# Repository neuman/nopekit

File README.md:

# nopekit

<p align="center">
<picture>
  <source media="(prefers-color-scheme: dark)" srcset="docs/img/nopey.png">
  
</picture>
</p>

## What Is Nopekit?

**Nopekit gives your AI agent engineering checks that can say “nope.”** It's a plugin for Claude Code, Codex and Cursor that helps you turn an idea into a physical design, test it against math, physics and engineering tools, and see what still needs work.

It's based on the [Grounding by Falsification](https://github.com/neuman/nopekit/blob/main/grounding_by_falsification.pdf) approach. AI has gotten very good at making believable proposals for all sorts of things both digital and physical but it is especially good at coding. The problem is that it's still not great at figuring out which proposals are actually good on its own. Grounding by falsification is the idea that we need to wrap AI with something outside itself that can check its work and say "nope" using trusted reasoning/math/physics/etc. Nopekit turns that approach into an extensible framework with room for plugins that can falsify proposals across any domain but especially physical design work.

**You describe what you want. The agent proposes a design. Independent checks try to break it.** Nopekit records the results and the reasons behind each design choice, then shows them on a project site. When the design changes, affected results become stale until checked again. Assumptions and tests that need a real prototype stay visible.

For example: “This shelf must carry 10 kg” becomes a load and a deflection limit. The agent designs a bracket; a beam check rejects it if it sags too far; a printability check rejects walls that are too thin. You can follow what failed, what changed, and why the next candidate is better.

[See It In Action](#see-it-in-action) · [Built In Packs](#built-in-packs) · [External Packs](#external-packs) · [Getting Started](#getting-started)

## See It In Action

**[PETGasus](https://neuman.github.io/PETGasusDrone/) is a quadcopter with a frame designed to print in one piece.** Its project site connects the design you can see with the requirements, decisions and evidence behind it.

[**Explore the live site →**](https://neuman.github.io/PETGasusDrone/) · [**Read the project repository →**](https://github.com/neuman/petgasusdrone)

The design history includes disconnected frames, thin walls and a frame that sagged far more than its optimizer predicted. Those rejected candidates are part of the record. The site shows what passed, what failed and what still waits on a physical build.

For smaller starting points, explore the [bracket example](examples/bracket/README.md), which runs without extra dependencies, or the [motorcycle airflow example](examples/motorbike/README.md), which uses OpenFOAM and ParaView.

## Built In Packs

Packs give the agent tools for a domain. A **proposer** makes a candidate; a **falsifier**, called a **gate**, checks it. One design can use several packs: a drone frame needs structural, printing, geometry and cost checks.

**Falsifiers**

These thirteen packs ship with Nopekit. The images show designs, results or illustrations of what each pack can check; click a pack name for its gates, sources, setup and limits.

| Example | Pack and what it checks | Basis and sources |
|---|---|---|
| <br>Check the exported shape with a different solver | [**topology-simp**](packs/topology-simp/PACK.md) · 4 gates<br>Material volume, static displacement and stress in a stated region. CalculiX meshes the exported STL independently of the optimizer; checks include mesh refinement and load equilibrium. | **3 established · 1 model-only**<br>trimesh and CalculiX results, with model-input guards. Requires trimesh, NumPy, Gmsh and CalculiX 2.21. Linear isotropic static checks; printing and physical tests remain separate. |
| <br>Air around a motorcycle and rider | [**aero-openfoam**](packs/aero-openfoam/PACK.md) · 9 gates<br>Drag, mesh quality, convergence and wall treatment for turbulent external flow. The motorcycle example's drag claim is still unresolved. | **3 established · 4 sourced · 2 model-only**<br>OpenFOAM; published domain, convergence and grid-error methods. Needs ESI OpenFOAM v2606; ParaView 6.2 for pictures. |
| <br>Do all these parts fit together? | [**cad-solid**](packs/cad-solid/PACK.md) · 8 gates<br>Closed solids, collisions, clearances, wall thickness and whether every part is held in the assembly. | **2 established · 6 model-only**<br>trimesh's volume verdict and manifold3d's clearance; Nopekit's geometry checks. Needs trimesh and NumPy; the clearance gate needs manifold3d and the wall gate SciPy or NetworkX. |
| <br>A drone frame designed to print in one piece | [**fdm-print**](packs/fdm-print/PACK.md) · 8 gates<br>Thin walls, overhangs, bridges, bed fit, layer direction, estimated print time and a slice on OrcaSlicer. | **8 model-only**<br>Printing heuristics with documented thresholds. Mesh checks need trimesh and NumPy; the slicer gate needs OrcaSlicer 2.4.2. A pass still needs a real print. |
| <br>The pack's own test board, as KiCad draws it | [**pcb-kicad**](packs/pcb-kicad/PACK.md) · 18 gates<br>Design rules with every custom rule probed, open connections, schematic agreement, pin names, trace heating, a fab's limits, circuit simulation, enclosure fit, land patterns against the vendor's drawing, a cell's charge window, charge limits, fault current and cutoff, connectors that can mate the wrong way, USB-C termination and radio antenna keep-outs. | **6 established · 9 sourced · 3 model-only**<br>KiCad, ngspice and CadQuery; IPC-2221, IEC 60949, the USB Type-C specification, module vendors' antenna guidance and fabricator limits. A clean rule check does not establish a correct circuit. |
| Firmware that CI really builds, that fits its flash, wakes from deep sleep and stays inside its radio grant | [**firmware-ci**](packs/firmware-ci/PACK.md) · 5 gates<br>A CI job that can read green on a failed build, then a replay of that job with act in its own containers: the build, the image against its flash region, the deep-sleep wake source and the Bluetooth LE transmit setting. The build and image checks serve any stack that builds in a GitHub Actions job on Linux; the wake rule covers ESP-IDF and ZMK, the transmit rule Zephyr, nRF Connect SDK and ESP-IDF on ESP32-C3 and S3, and each skips other stacks by name. | **1 established · 4 sourced**<br>The toolchain's own exit code in the job's container; GitHub's documented shell behaviour, the bootloader's or partition table's layout, and each stack's sleep and Kconfig sources. Needs act 0.2.97, Docker and Git, plus PyYAML; the baseline's ESP-IDF image is about 5.4 GB. The transmit limit is your claim: the pack cannot say which radio grant applies. |
| Can the smallest hands in the range reach every control? | [**hand-ergonomics**](packs/hand-ergonomics/PACK.md) · 2 gates<br>The share of a measured population whose thumb or index finger reaches every control from its grip, counted subject by subject, on a declared layout that must match the exported scene. | **1 sourced · 1 model-only**<br>ANSUR 1988's per-subject hand data (public domain), shipped with its hashes. The reach count needs no extra dependencies; the layout check needs trimesh, NumPy and manifold3d. Comfort, width and mass stay with a person who holds a print. |
| <br>Beam-pack baseline, illustrated | [**beam-analytic**](packs/beam-analytic/PACK.md) · 8 gates<br>Bending, sag, buckling, shear and fastener bearing, with guards on where beam theory applies. | **7 sourced · 1 model-only**<br>Standard strength-of-materials formulae. No extra dependencies. Applies to beam-like members, not arbitrary meshes. |
| <br>Pressure loss through an oil channel | [**cfd-openfoam**](packs/cfd-openfoam/PACK.md) · 6 gates<br>Laminar pressure drop after checking flow regime, mesh quality, convergence and mesh independence. | **3 established · 2 sourced · 1 model-only**<br>OpenFOAM and published grid-convergence methods. Needs ESI OpenFOAM v2606; ParaView 6.2 for pictures. |
| <br>Solar charging over two weeks | [**thermal-analytic**](packs/thermal-analytic/PACK.md) · 11 gates<br>Heat loss, cooling, temperature, fins, solar collection, stagnation and a sealed handheld's average skin temperature. | **10 sourced · 1 model-only**<br>Heat-transfer correlations; Duffie & Beckman and ASHRAE solar models. No extra dependencies. |
| <br>A solar Stirling system over a day | [**openmodelica**](packs/openmodelica/PACK.md) · 8 gates<br>Equation balance, compilation, simulation completion and simulated values against their limits. | **4 established · 4 model-only**<br>OpenModelica's own checks and results, plus source and consistency checks. Solver gates need `omc`. |
| <br>A hull that must float and stay upright | [**fluids-analytic**](packs/fluids-analytic/PACK.md) · 7 gates<br>Buoyancy, freeboard, stability, drag and pipe pressure loss. | **7 sourced**<br>Textbook hydrostatics and flow correlations, within their stated regimes. No extra dependencies. |
| <br>The whole build against its budget | [**sourcing**](packs/sourcing/PACK.md) · 7 gates<br>Missing prices, cost overruns, lead times, minimum orders and single-source parts. | **1 sourced · 6 model-only**<br>Vendor process rules and procurement checks on your recorded bill of materials. Offline; no live stock search. No extra dependencies. |

**How much should you trust a check?** Each gate declares where its logic comes from:

- **Established:** an existing tool's own verdict, such as KiCad's design-rule check. Trust extends as far as that tool and the problem you gave it.
- **Sourced:** a formula or rule from a cited textbook, standard or datasheet. Trust depends on the source and its range of applicability.
- **Model-only:** logic without an independent source. Its controls show it can fail; they do not establish that its reasoning is correct.

Before a gate's passes count, it must pass a known-good input and reject a known-bad one. That qualification is separate from its basis. **Skipped, crashed and stale checks never count as passes.** The report shows both the outcome and the basis so you can judge the evidence.

**Proposers**

The agent itself is the everyday proposer, writing and changing your design. Built-in packs also ship dedicated proposal tools:

| Example | Proposer | Tool and trust |
|---|---|---|
| <br>Find where the material earns its weight | [**topology-simp: 3D topology optimization**](packs/topology-simp/PACK.md)<br>Give it loads, supports, keep-outs and a material budget. SIMP proposes a 3D density field for your model to turn into a part. | **Sourced:** SIMP, density filtering and projection from published methods. Extracted from PETGasus. NumPy, SciPy and Numba; pyamg for larger solves. Its own score is a proposal, never structural proof. |
| <br>The pack's test board, routed again | [**pcb-kicad: autoroute**](packs/pcb-kicad/PACK.md)<br>Turn an unrouted KiCad board into a routed candidate. | **Freerouting**, an established autorouter. Its output is a proposal; KiCad gates check the adopted board. Requires pcbnew, Java and Freerouting. |
| Schematic for a generated board | [**pcb-kicad: schematic_from_board**](packs/pcb-kicad/PACK.md)<br>Write a KiCad schematic from a board's pad nets, so ERC, parity and pin names can run on a board with no drawn schematic. | **Model-only:** this pack's own writer, on KiCad's stock symbols mapped by a person part by part. Its output is a proposal; KiCad's parity check compares the adopted schematic with the board. Needs only KiCad's symbol library. |
| Power records for a board that carries a cell | [**pcb-kicad: battery_record_draft**](packs/pcb-kicad/PACK.md)<br>Draft the cell, charger, protector, conductor, mating, USB-C and rail records that the power rules read, from a board's parts, pin names and copper. | **Model-only:** this pack's own reader of the board. Every datasheet number, choice and source is left as a FILL value, and every power rule refuses the draft until a person fills them. Standard library only. |
| Where each thumb reaches on the face | [**hand-ergonomics: reach_envelope**](packs/hand-ergonomics/PACK.md)<br>Map where each grip's thumb and index finger reach, as a share of the population; count how many controls of a pitch fit in reach; give the grip spacing and design ranges for hand size. | **Sourced:** ANSUR 1988's per-subject hand data, the table `ergo.digit_reach` counts. A share on the map is for one point; the gate counts every control at once. Its maps are proposals; the reach gate judges the layout you adopt. matplotlib draws the map where it is installed. |

## External Packs

**A pack can live in its own Git repository.** You can share domain knowledge, wrap another engineering tool, or keep a project's custom checks alongside its design without changing Nopekit itself.

A standalone pack has a `pack.json` manifest, a `PACK.md` explaining its scope, and the gates, proposers, references and test fixtures it needs. Clone it into your project's `.nopekit/packs/<pack-name>/`, or into `~/.nopekit/packs/<pack-name>/` to make it discoverable across projects. `NOPEKIT_PACK_PATH` can point to other directories containing packs.

Then enable it by the name in its manifest:

```sh
nopekit packs list
nopekit packs validate <pack-name>
nopekit packs add <pack-name>
nopekit gate selftest --pack <pack-name>
```

`packs add` enables a discovered pack for the current project; cloning and updating its repository are separate steps. External gates also face mutation checks: Nopekit perturbs values from their known-good inputs to test whether the gates reject violations.

External packs can add specialized falsifiers, such as a product's crash or vibration tests, and proposal tools for domains the built-in packs do not yet cover.

To build your own, ask the agent to use Nopekit's **pack-authoring** skill. The [pack format](docs/PACK_FORMAT.md) defines the interface and the [extension protocol](docs/EXTENSION_PROTOCOL.md) explains how to develop and qualify a new capability.

## Getting Started

### 1. Install Nopekit

Nopekit is one plugin for three agents: the repository root holds a manifest for each
(`.claude-plugin/`, `.codex-plugin/`, `.cursor-plugin/`), and they share the same skills
and the same end-of-turn hook, which records each round.

**Claude Code.** Ask it:

> Install the Nopekit plugin from `https://github.com/neuman/nopekit` and help me get it ready to use.

Or install it directly with Claude Code's plugin commands:

```text
/plugin marketplace add neuman/nopekit
/plugin install nopekit
```

**Codex.** Codex reads the same marketplace:

```bash
codex plugin marketplace add neuman/nopekit
codex plugin add nopekit@nopekit
```

Codex runs a plugin's hook only after you review and trust it, and asks again after
every update of the plugin. Until you do, rounds are not recorded at the end of a turn;
`nopekit round --commit` records one by hand.

**Cursor.** Clone the plugin into Cursor's local plugins, then restart Cursor:

```bash
git clone --depth 1 https://github.com/neuman/nopekit ~/.cursor/plugins/local/nopekit
```

To update, `git -C ~/.cursor/plugins/local/nopekit pull` and restart. Cursor can also
import the Claude Code plugin; install it one way, not both, or each turn ends with two
rounds.

You'll need Python 3.10 or newer available as `python3`. Nopekit's core has no third-party Python dependencies. Some checks need optional tools or packages; the agent should tell you when one is needed. For mesh checks used in 3D printing and solid-part work, install:

```sh
pip install trimesh numpy
```

### 2. Bring an idea

Open your agent in a project directory and say:

> I want to use Nopekit to design something new. Interview me about the idea, one question at a time. Help me turn what I want into requirements, explore possible designs, set up the project and its checks, and launch the project site so I can understand the design and follow its progress.

You can start with an empty folder, a sketch, existing CAD files or a half-finished design. The agent helps choose the relevant packs and explains any tools they need.

## Using Nopekit Step By Step

You work through this in conversation. The agent operates the tools; the project site lets you follow the work and question its conclusions.

1. **Describe the thing you want.** Say what it does, where it goes and what matters: size, load, price, materials, power or feel. The agent helps make those requirements concrete.
2. **Decide what would count as success.** Turn requirements into testable claims: “sags no more than 0.5 mm,” “fits this printer,” “costs under $150.” Identify which need calculations, simulations, measurements or human judgment.
3. **Explore candidates.** The agent builds the model or runs a proposer. It records the choices, their reasons and the alternatives that lost, so the next iteration can build on what you learned.
4. **Run checks and inspect failures.** Gates compare the candidate with its limits. Follow the evidence on the site, challenge assumptions, change the design and run again. A missing solver stays visible as a skipped check.
5. **Review what is ready.** The report separates current checks from assumptions, unresolved claims and physical tests. Changing the design invalidates affected evidence. Each milestone names what must be established before you spend on a prototype or fabrication.
6. **Build, measure and feed the results back.** Export reruns the required checks before producing a package. Record what happened to the real article; a physical failure becomes evidence for the next design. A simulation pass alone never establishes how the built object behaves.

### Run checks and read the results

A check, or **gate**, evaluates a specific claim against the current inputs. Results are recorded with their provenance. A result may be useful without being a pass: it can reveal a failure, expose a missing capability, or show that an earlier result is now stale.

Here are the important distinctions:

| Status | What it means |
|---|---|
| **Checked** | A qualified gate passed on the inputs that apply to the current candidate. This is evidence for the claim the gate tests—not a guarantee that the whole product works. |
| **Failing** | A gate found a problem with the current candidate. Use the detail to decide what to change or investigate. |
| **Gap** | No suitable qualified gate currently settles the claim. The claim remains unresolved. |
| **Open** | A gate exists, but hasn't produced a current result for the inputs. |
| **Stale** | A gate passed earlier, but something it depended on has changed. The old result doesn't establish the claim for the current candidate. |
| **Skipped** | The gate was skipped, often because a required tool or dependency is missing. Nothing was established by that run. |
| **Skipped (errored)** | The gate crashed. Treat the result as unresolved, not as a pass. |
| **Pending build / physical** | The claim needs evidence from building or testing the real thing. Software checks cannot substitute for that evidence. |
| **Assumed** | The project is relying on something that has not yet been established by a qualifying check. |

The key habit is to ask: **What exactly does this result establish, and what does it leave open?** A clean CAD check isn't proof that a physical part will behave as intended. A simulation result isn't a real-world measurement. A claim with no check isn't checked just because the design looks plausible.

<details>
<summary>Useful commands when you want to inspect the project directly</summary>

| Command | What it tells you or does |
|---|---|
| `nopekit status` | Current claims and their statuses. |
| `nopekit check` | Run the project's gates. |
| `nopekit report` | Readiness and the evidence behind it. |
| `nopekit why <name>` | Why a parameter, claim, requirement or decision is there. |
| `nopekit gap --propose` | Claims whose mechanism has yet to run, and packs that might help. |
| `nopekit doctor` | Diagnose the environment, model and records. |
| `nopekit site serve --watch --detach` | Open a local server that watches project changes. |
| `nopekit site serve --stop` | Stop the detached server. |
| `nopekit --help` | All commands and options. |

</details>

## More Detail

- [The method](METHOD.md) — the principles Nopekit makes mechanical.
- [Pack format](docs/PACK_FORMAT.md) — gates, proposers, controls and source declarations.
- [Extension protocol](docs/EXTENSION_PROTOCOL.md) — developing new capabilities.
- [Site contract](docs/SITE_CONTRACT.md) — how the site represents designs and evidence.
- [Spine contract](docs/SPINE_CONTRACT.md) — the engine, records and its limits.
- [Origins](docs/ORIGINS.md) — the experience behind the method.
- [Grounding by Falsification paper](grounding_by_falsification.pdf) — the underlying approach.
- [Contributing](CONTRIBUTING.md) — working on Nopekit itself.

## Status and License

Nopekit is an early project. The core engine and bundled packs work, but interfaces may change and the range of supported checks is still growing. Use it, inspect it, fork it, and tell us what breaks.

Licensed under the [Apache License 2.0](LICENSE).

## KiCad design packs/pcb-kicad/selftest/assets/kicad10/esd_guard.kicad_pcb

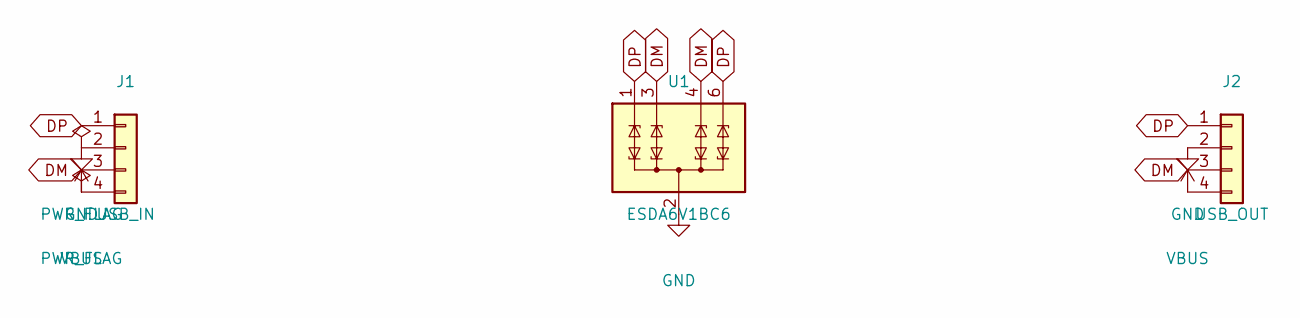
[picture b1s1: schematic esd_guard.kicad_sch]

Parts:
J1: USB_IN; PinHeader_1x04_P2.54mm_Vertical
J2: USB_OUT; PinHeader_1x04_P2.54mm_Vertical
U1: ESDA6V1BC6; SOT-23-6

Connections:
DM: J1.3, J2.3, U1.3 (TVS2), U1.4 (TVS3)
DP: J1.1, J2.1, U1.1 (TVS1), U1.6 (TVS4)
GND: J1.2, J2.2, U1.2 (COM), U1.5 (COM)
VBUS: J1.4, J2.4

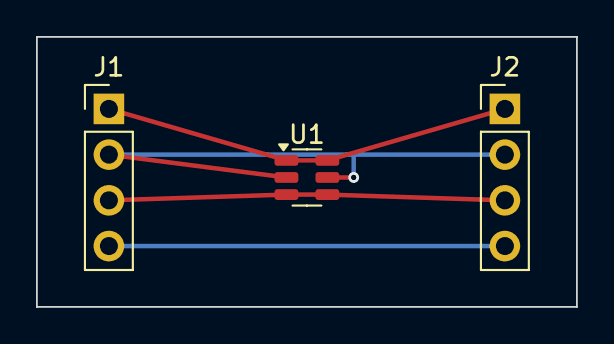
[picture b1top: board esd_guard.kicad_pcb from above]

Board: 2 copper layers, 30.0 x 15.0 mm, 3 parts (0 on the bottom side), 4 nets.

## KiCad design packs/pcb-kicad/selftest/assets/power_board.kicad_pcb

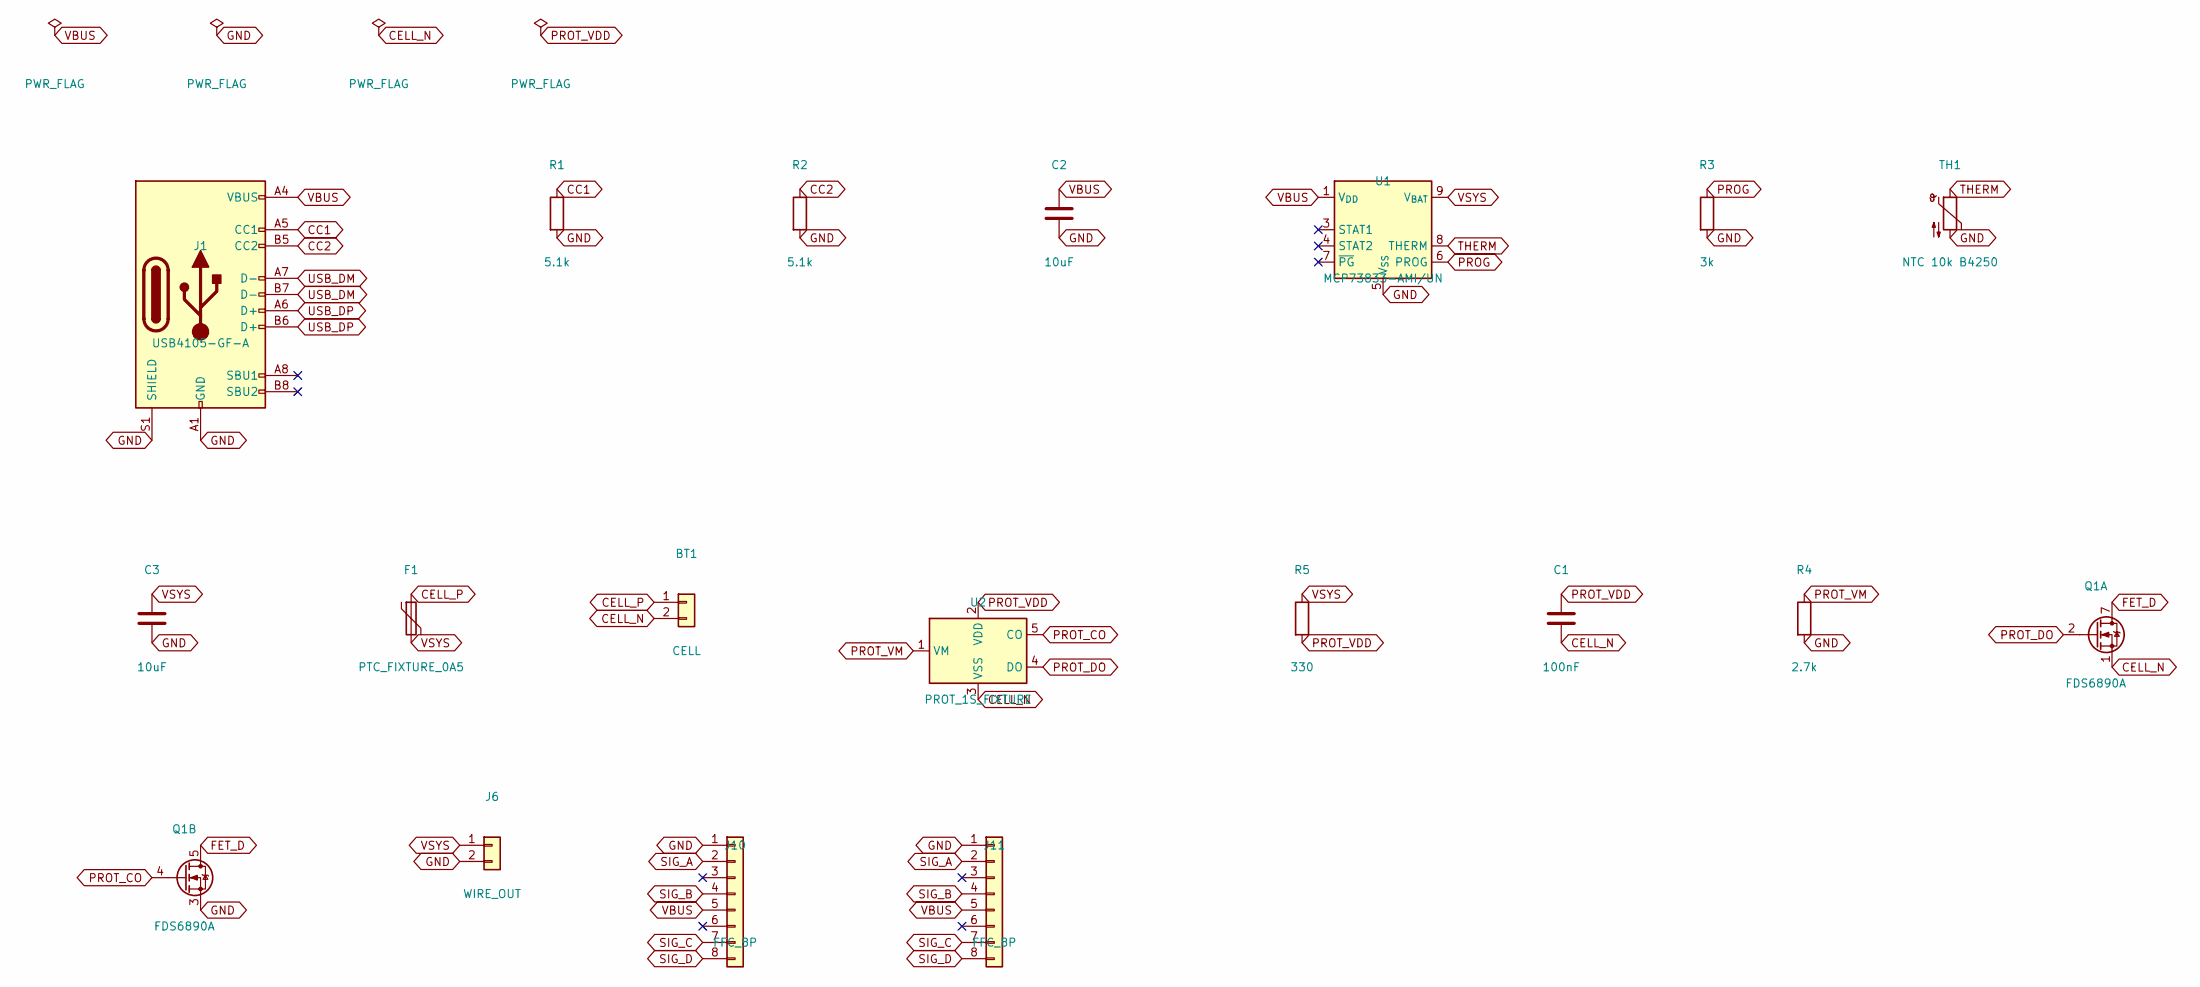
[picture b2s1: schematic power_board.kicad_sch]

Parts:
BT1: CELL; Molex_Micro-Latch_53253-0270_1x02_P2.00mm_Vertical
C1: 100nF; C_0603_1608Metric
C2, C3: 10uF; C_0603_1608Metric
F1: PTC_FIXTURE_0A5; Fuse_1206_3216Metric
J1: USB4105-GF-A; USB_C_Receptacle_GCT_USB4105-xx-A_16P_TopMnt_Horizontal
J6: WIRE_OUT; PinHeader_1x02_P2.54mm_Vertical
J10, J11: FFC_8P; Hirose_FH12-8S-0.5SH_1x08-1MP_P0.50mm_Horizontal
Q1: FDS6890A; SOIC-8_3.9x4.9mm_P1.27mm
R1, R2: 5.1k; R_0603_1608Metric
R3: 3k; R_0603_1608Metric
R4: 2.7k; R_0603_1608Metric
R5: 330; R_0603_1608Metric
TH1: NTC 10k B4250; R_0603_1608Metric
U1: MCP73833-AMI/UN; MSOP-10_3x3mm_P0.5mm
U2: PROT_1S_FIXTURE; SOT-23-5

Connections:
CC1: J1.A5 (CC1), R1.1
CC2: J1.B5 (CC2), R2.1
CELL_N: BT1.2, C1.2, Q1.1 (S1), U2.3 (VSS)
CELL_P: BT1.1, F1.1
FET_D: Q1.5 (D2), Q1.6 (D2), Q1.7 (D1), Q1.8 (D1)
GND: C2.2, C3.2, J1.A1 (GND), J1.A12 (GND), J1.B1 (GND), J1.B12 (GND), J1.S1 (SHIELD), J6.2, J10.1, J11.1, Q1.3 (S2), R1.2, R2.2, R3.2, R4.2, TH1.2, U1.5 (V_{SS})
PROG: R3.1, U1.6 (PROG)
PROT_CO: Q1.4 (G2), U2.5 (CO)
PROT_DO: Q1.2 (G1), U2.4 (DO)
PROT_VDD: C1.1, R5.2, U2.2 (VDD)
PROT_VM: R4.1, U2.1 (VM)
SIG_A: J10.2, J11.2
SIG_B: J10.4, J11.4
SIG_C: J10.7, J11.7
SIG_D: J10.8, J11.8
THERM: TH1.1, U1.8 (THERM)
USB_DM: J1.A7 (D-), J1.B7 (D-)
USB_DP: J1.A6 (D+), J1.B6 (D+)
VBUS: C2.1, J1.A4 (VBUS), J1.A9 (VBUS), J1.B4 (VBUS), J1.B9 (VBUS), J10.5, J11.5, U1.1 (V_{DD}), U1.2 (V_{DD})
VSYS: C3.1, F1.2, J6.1, R5.1, U1.9 (V_{BAT}), U1.10 (V_{BAT})

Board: 2 copper layers, 18 parts (0 on the bottom side), 20 nets, no tracks yet.

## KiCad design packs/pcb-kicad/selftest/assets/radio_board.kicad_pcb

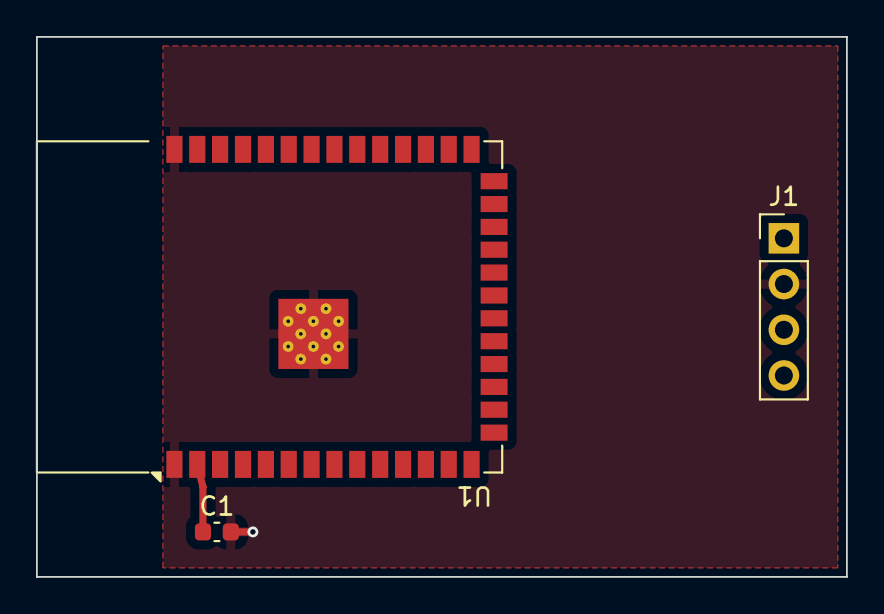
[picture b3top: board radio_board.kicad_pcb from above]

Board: 4 copper layers, 45.0 x 30.0 mm, 3 parts (0 on the bottom side), 3 nets.

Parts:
C1: 10uF; C_0603_1608Metric
J1: CONN_4; PinHeader_1x04_P2.54mm_Vertical
U1: ESP32-S3-WROOM-1

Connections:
3V3: C1.1, J1.1, U1.2 (3V3)
EN: J1.3, U1.3 (EN)
GND: C1.2, J1.2, U1.1 (GND), U1.40 (GND), U1.41 (GND)

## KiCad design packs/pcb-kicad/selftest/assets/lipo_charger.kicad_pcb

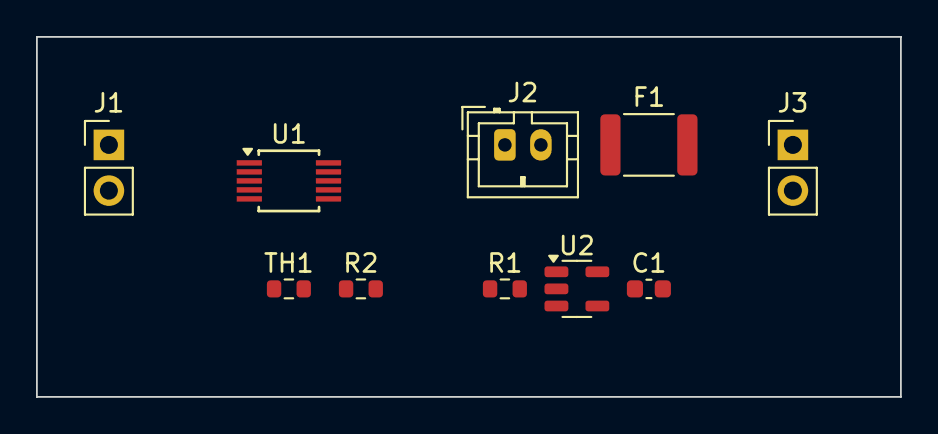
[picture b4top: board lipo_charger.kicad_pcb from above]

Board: 2 copper layers, 48.0 x 20.0 mm, 10 parts (0 on the bottom side), 7 nets, no tracks yet.

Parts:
C1: 100nF; C_0603_1608Metric
F1: MF-MSMF075; Fuse_1812_4532Metric
J1: VBUS_IN; PinHeader_1x02_P2.54mm_Vertical
J2: CELL; JST_PH_B2B-PH-K_1x02_P2.00mm_Vertical
J3: WIRE_OUT; PinHeader_1x02_P2.54mm_Vertical
R1: 330; R_0603_1608Metric
R2: 2k; R_0603_1608Metric
TH1: NTC_10k; R_0603_1608Metric
U1: MCP73833; MSOP-10_3x3mm_P0.5mm
U2: AP9101CK; SOT-23-5

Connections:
CUT_VDD: C1.1, R1.2, U2.2 (VDD)
GND: C1.2, J1.2, J2.2, J3.2, R2.2, TH1.2, U1.5 (V_{SS}), U2.1 (VM), U2.3 (VSS)
PROG: R2.1, U1.6 (PROG)
THERM: TH1.1, U1.8 (THERM)
VBAT_OUT: F1.2, J3.1
VBUS: J1.1, U1.1 (V_{DD}), U1.2 (V_{DD})
VCELL: F1.1, J2.1, R1.1, U1.9 (V_{BAT}), U1.10 (V_{BAT})
